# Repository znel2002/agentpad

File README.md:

# AgentPad

A 9-key macropad + rotary encoder + OLED for driving **AI coding agents** — Claude Code, Codex CLI, and Cursor. Firmware-native (no host daemon), vendor-neutral, with a per-tool **LAYER** key instead of app-detection. Built for **Hack Club Hackpad**.

## What it does

Nine keys mapped to the actions you hit dozens of times an hour when driving an agent, plus a rotary dial and a status screen:

| | | |
|---|---|---|
| **STOP** (interrupt) | **YES** (approve) | **NO** (reject) |
| **PLAN** (mode toggle) | **NEW** (`/clear`) | **TALK** (push-to-talk) |
| **RUN** (test/last cmd) | **COMPACT** (`/compact`) | **LAYER** (switch tool) |

- **Encoder** — turn = model / reasoning-effort dial.
- **OLED** — shows the active tool profile + mode.
- **LAYER key** — cycles per-tool keymaps: **Claude Code → Codex → Cursor → shell**. Each key sends that tool's real shortcut; hold-LAYER reaches secondary actions (accept-edit, reject-edit, resume, background). No daemon, no app-detection.

Full keymap + pin map: [docs/DESIGN-SPEC.md](docs/DESIGN-SPEC.md). Keymap logic is unit-tested: [Firmware/tests/sim_keymap.py](Firmware/tests/sim_keymap.py).

## Hardware

- **MCU:** Seeed XIAO RP2040 (all 11 GPIO used)
- **Keys:** 9× MX in a 3×3 diode matrix (9× 1N4148, COL2ROW)
- **Encoder:** 1× EC11 (turn-only)
- **Display:** 1× 0.91" SSD1306 OLED (I2C)
- **Firmware:** KMK (CircuitPython)
- **RGB:** deferred to v2 (v1 ships without LEDs)

## Renders & proof

**Exploded — top plate / PCB / bottom tray**

**Schematic**

**PCB — DRC passes with 0 errors**

## Bill of Materials

All parts come from the free Hackpad kit (nothing self-sourced):

| Part | Qty | Notes |
|---|---|---|
| Seeed XIAO RP2040 | 1 | microcontroller |
| 1N4148 diode | 9 | switch matrix, COL2ROW, `D_DO-35_SOD27_P7.62mm` |
| MX-style switch | 9 | solder-in, 3×3 grid @ 19.05 mm |
| EC11 rotary encoder | 1 | model / effort dial |
| 0.91" OLED (SSD1306) | 1 | I2C, pin order GND-VCC-SCL-SDA |
| DSA blank keycap | 9 | color/legend via a printed card |
| M3 screw | 4 | lid → base corner posts |

## Repo structure

```
CAD/         agentpad-case.f3d (Fusion source), agentpad_assembly.step/.3mf (case + real PCB), board STEP
PCB/         KiCad project — schematic, board (DRC 0 errors), Hack Club care-package libs
Firmware/    KMK source (kmk/main.py) + keymap simulation test
production/  gerbers.zip, top_plate.stl, bottom_tray.stl, main.py
docs/        DESIGN-SPEC, BUILD-PLAN, screenshots
```

## Firmware (KMK)

Flash CircuitPython to the XIAO, copy the KMK `kmk/` folder + libs + [`Firmware/kmk/main.py`](Firmware/kmk/main.py) to the `CIRCUITPY` drive. Details + per-layer keystroke tables: [Firmware/README.md](Firmware/README.md).

## Case

3D-printed two-part sandwich — **top lid + bottom base** — designed in **Autodesk Fusion** ([CAD/agentpad-case.f3d](CAD/agentpad-case.f3d)) around the exact PCB (imported as STEP). Both parts print flat with no supports.

- **Lid:** recessed key well inside a raised bezel; 9 switch cutouts with chamfered mouths, an encoder hole, and an OLED window; rounded R6 corners.
- **Base:** holds the PCB on corner posts; USB-C exits a slot in the side wall; **AgentPad** engraved on the front wall; matching R6 corners and chamfered top edge.
- **Assembly:** 4× M3 screws through the lid into the base's corner posts.

Fit is verified against the real board geometry — switch cutouts sit exactly on the switch stems, and screw holes align to the base bosses.

## License

MIT — see notes; the vendored Hack Club care package under `PCB/lib/` retains its own license.

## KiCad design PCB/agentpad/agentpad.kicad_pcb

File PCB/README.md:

# PCB — AgentPad

KiCad source for the AgentPad board. Design locked in
[../docs/DESIGN-SPEC.md](../docs/DESIGN-SPEC.md).

## Before you start
1. KiCad **10.0.5** is installed. Its libraries are forward-compatible, so the
   care package (authored on an older version) loads fine — no version issue.
2. Download + install the libraries here:
   - **Care package** (XIAO symbol + footprints): https://github.com/hackclub/hackpad/releases/tag/v0.1-bugfix → `kicad_care_package.zip`
   - XIAO footprints (backup): https://github.com/Seeed-Studio/OPL_Kicad_Library
   - MX switch footprints: https://github.com/ai03-2725/MX_V2
   - Rotary encoder: https://kicad.github.io/footprints/Rotary_Encoder
   - 0.91" OLED (4-pin): https://github.com/gorbachev/KiCad-SSD1306-0.91-OLED-4pin-128x32.pretty
   - The `.sym` files are symbol libs; the `.pretty` folders are footprint libs
     (Preferences → Manage Symbol/Footprint Libraries → add).
3. **Reference board** — the guide author's macropad (OLED + encoder + matrix +
   SK6812, closest to ours): https://github.com/hackclub/hackpad/tree/clean/extras/orpheuspad
4. Learn the flow: ai03's PCB guide https://wiki.ai03.com/books/pcb-design
5. Build the 3-key tutorial board first (XIAO symbol = `MODULE-SEEEDUINO-XIAO`,
   switches = `SW_Push`) to validate the toolchain, then extend to this net map.

## Net map — XIAO RP2040 pad → net (all 11 GPIO used)

| Pad | GPIO | Net |
|---|---|---|
| D0 | GP26 | ROW0 |
| D1 | GP27 | ROW1 |
| D2 | GP28 | ROW2 |
| D3 | GP29 | LED_DIN (SK6812 chain data-in) |
| D4 | GP6 | OLED_SDA (I2C) |
| D5 | GP7 | OLED_SCL (I2C) |
| D6 | GP0 | COL0 |
| D7 | GP1 | COL1 |
| D8 | GP2 | COL2 |
| D9 | GP4 | ENC_A |
| D10 | GP3 | ENC_B |
| 3V3 | — | OLED VCC |
| **5V** | — | **all SK6812 VCC** (the LEDs are 5V parts, per the Hackpad add-components page) |
| GND | — | matrix/encoder commons, OLED GND, all SK6812 GND |

> Data logic stays at the XIAO's 3.3V; SK6812 run their VCC at 5V (the XIAO's 5V/USB
> pad). This is how the kit is designed — do not put SK6812 VCC on 3V3.

## Exact symbols / footprints (confirmed on hackpad.hackclub.com/add-components)

Verified against the unpacked care package in `lib/kicad_care_package/`. The care
package holds **only** the XIAO + SK6812; everything else is a KiCad built-in lib.

| Part | Symbol | Footprint | Source |
|---|---|---|---|
| XIAO RP2040 | `MOUDLE-SEEEDUINO-XIAO` *(sic — typo is in the file, search it literally)* | `XIAO-Generic-Hybrid-14P-2.54-21X17.8MM` | care package |
| SK6812 MINI-E | `SK6812MINI-E` | `SK6812MINI-E_fixed` | care package |
| MX switch | `SW_Push` | `ai03-2725/MX_V2` (or KiCad `Button_Switch_Keyboard`) | KiCad / MX_V2 |
| Diode 1N4148 | `D` | `Diode_THT:D_DO-35_SOD27_P7.62mm_Horizontal` (don't go shorter) | KiCad built-in |
| EC11 encoder | `RotaryEncoder_Switch` | `RotaryEncoder_Alps_EC11E-Switch_Vertical_H20mm` | KiCad built-in |
| 0.91" OLED | 4-pin header (`Connector_Generic`) | `PinHeader_1x04_P2.54mm_Vertical` | KiCad built-in |

No pull-up resistors anywhere — the RP2040 has internal pull-ups (kit relies on this).

## Matrix (3×3, 9 keys)
- One **1N4148** (onsemi) per key, all the **same orientation (COL2ROW)**. Wrong
  diode direction is the #1 beginner failure — verify against the KMK config
  (`Firmware/kmk/main.py`, `diode_orientation = COL2ROW`). The physical diode has
  a **black bar** marking the cathode.
- Footprint `Diode_THT:D_DO-35_SOD27_P7.62mm_Horizontal`.
- Keys map row-major to the keymap: R1C1..R1C3, R2C1..R2C3, R3C1..R3C3.

## Encoder (EC11E, 20 mm D-shaft)
- Symbol `RotaryEncoder_Switch`, footprint `RotaryEncoder_Alps_EC11E-Switch_Vertical_H20mm`.
- A → ENC_A (D9), B → ENC_B (D10), common → GND. No pull-ups needed.
- **Turn-only config:** the footprint includes the push-switch pins — leave them
  **unconnected**. Keeping the pads means an 8-key clickable variant is possible
  later without a respin.

## OLED (0.91" 128×32 SSD1306, I2C @ 0x3C)
- Footprint = plain **2.54 mm 4-pin header** (the module has a standard header;
  no special footprint needed).
- **Pin order GND-VCC-SCL-SDA** — match it exactly (online pinouts vary).
- SDA→D4, SCL→D5, VCC→3V3, GND→GND. No pull-ups needed.

## SK6812 MINI-E chain (20 LEDs, 1 data line)
- Footprint `SK6812MINI-E` from the care package (**not** `SK6812MINI`; symbol +
  both footprints must say MINI-E).
- 4 pins: VCC (**5V**), GND, DIN, DOUT. D3 → LED1 DIN; each DOUT → next DIN; chain all 20.
- **Orientation: the notch/cut is on the bottom-right corner** — wrong rotation and
  the LEDs won't light. Keep every LED the same way.
- 9 per-key (under each switch) + up to 11 case underglow.
- Keep the data trace from the XIAO to LED1 short.

## Mounting holes (from the Hackpad resources page)
- Use KiCad's **M3 mounting-hole footprint** — NOT Edge.Cuts.
- 6 holes to match the 6× M3 screws / heatset inserts.
- For the OLED, a plain **4-pin header footprint** is fine (order GND-VCC-SCL-SDA).

## Routing tips (from the resources page)
- Try to route everything on **one layer** first; only drop to the 2nd layer to
  avoid a big loop. Keeps the board clean.
- After routing: **Tools → Cleanup Tracks & Vias** (press "Build changes" twice).
- Export the PCB to PDF and print 1:1 to sanity-check physical measurements.

## Preflight before ordering
- [ ] Board ≤ 100 × 100 mm, **2 layers**.
- [ ] `AgentPad` on the silkscreen.
- [ ] 6× M3 mounting-hole footprints placed.
- [ ] **DRC → 0 errors** (reviewers check this).
- [ ] Export gerbers → `../production/gerbers.zip`.
- [ ] Order JLCPCB immediately after DRC is clean.

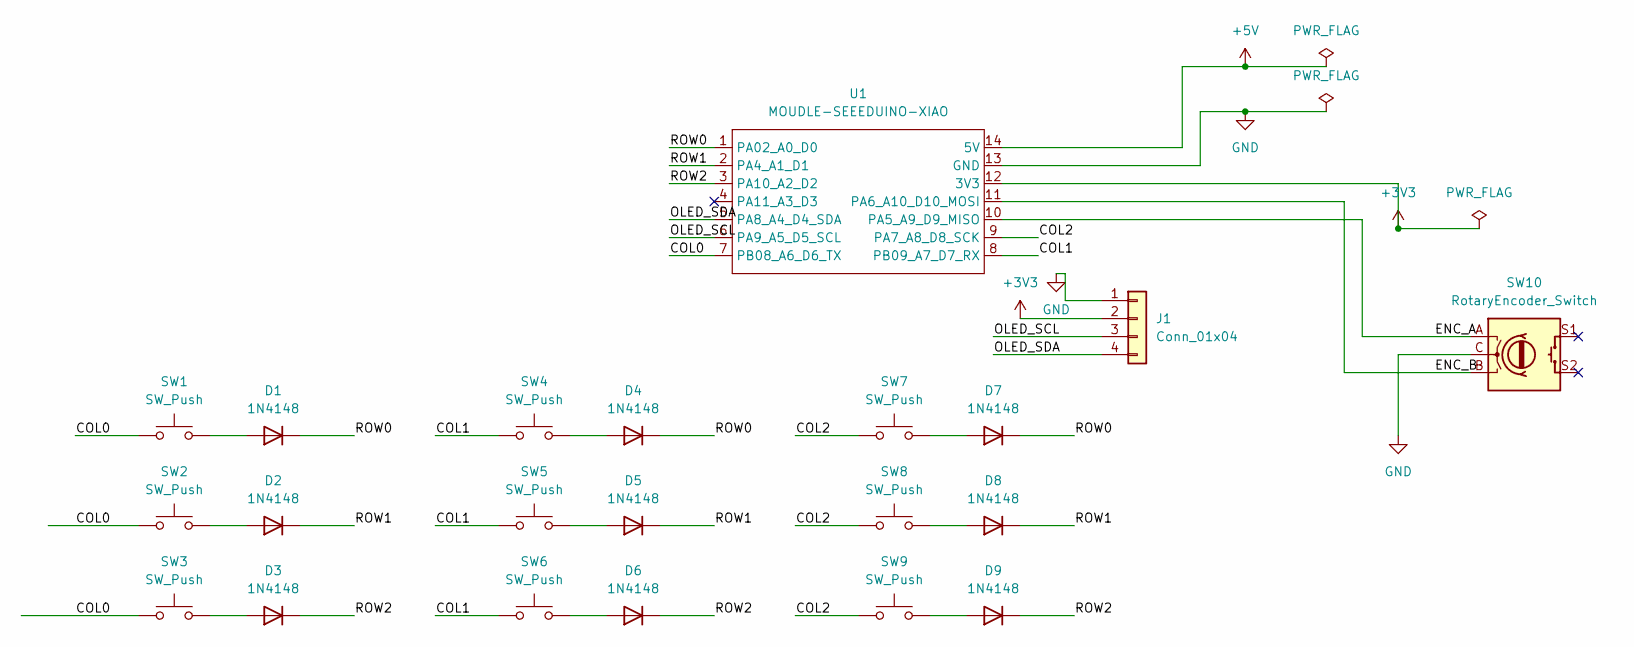
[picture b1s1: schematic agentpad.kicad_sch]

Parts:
D1, D2, D3, D4, D5, D6, D7, D8, D9: 1N4148; D_DO-35_SOD27_P7.62mm_Horizontal
J1: Conn_01x04; PinHeader_1x04_P2.54mm_Vertical
SW1, SW2, SW3, SW4, SW5, SW6, SW7, SW8, SW9: SW_Push; SW_Cherry_MX_1.00u_PCB
SW10: RotaryEncoder_Switch; RotaryEncoder_Alps_EC11E-Switch_Vertical_H20mm
U1: MOUDLE-SEEEDUINO-XIAO; XIAO-Generic-Hybrid-14P-2.54-21X17.8MM

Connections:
+3V3: J1.2, U1.12 (3V3)
+5V: U1.14 (5V)
/COL0: SW1.1, SW2.1, SW3.1, U1.7 (PB08_A6_D6_TX)
/COL1: SW4.1, SW5.1, SW6.1, U1.8 (PB09_A7_D7_RX)
/COL2: SW7.1, SW8.1, SW9.1, U1.9 (PA7_A8_D8_SCK)
/ENC_A: SW10.A, U1.10 (PA5_A9_D9_MISO)
/ENC_B: SW10.B, U1.11 (PA6_A10_D10_MOSI)
/OLED_SCL: J1.3, U1.6 (PA9_A5_D5_SCL)
/OLED_SDA: J1.4, U1.5 (PA8_A4_D4_SDA)
/ROW0: D1.1 (K), D4.1 (K), D7.1 (K), U1.1 (PA02_A0_D0)
/ROW1: D2.1 (K), D5.1 (K), D8.1 (K), U1.2 (PA4_A1_D1)
/ROW2: D3.1 (K), D6.1 (K), D9.1 (K), U1.3 (PA10_A2_D2)
GND: J1.1, SW10.C, U1.13 (GND)
unnamed: D1.2 (A), SW1.2
unnamed: D2.2 (A), SW2.2
unnamed: D3.2 (A), SW3.2
unnamed: D4.2 (A), SW4.2
unnamed: D5.2 (A), SW5.2
unnamed: D6.2 (A), SW6.2
unnamed: D7.2 (A), SW7.2
unnamed: D8.2 (A), SW8.2
unnamed: D9.2 (A), SW9.2

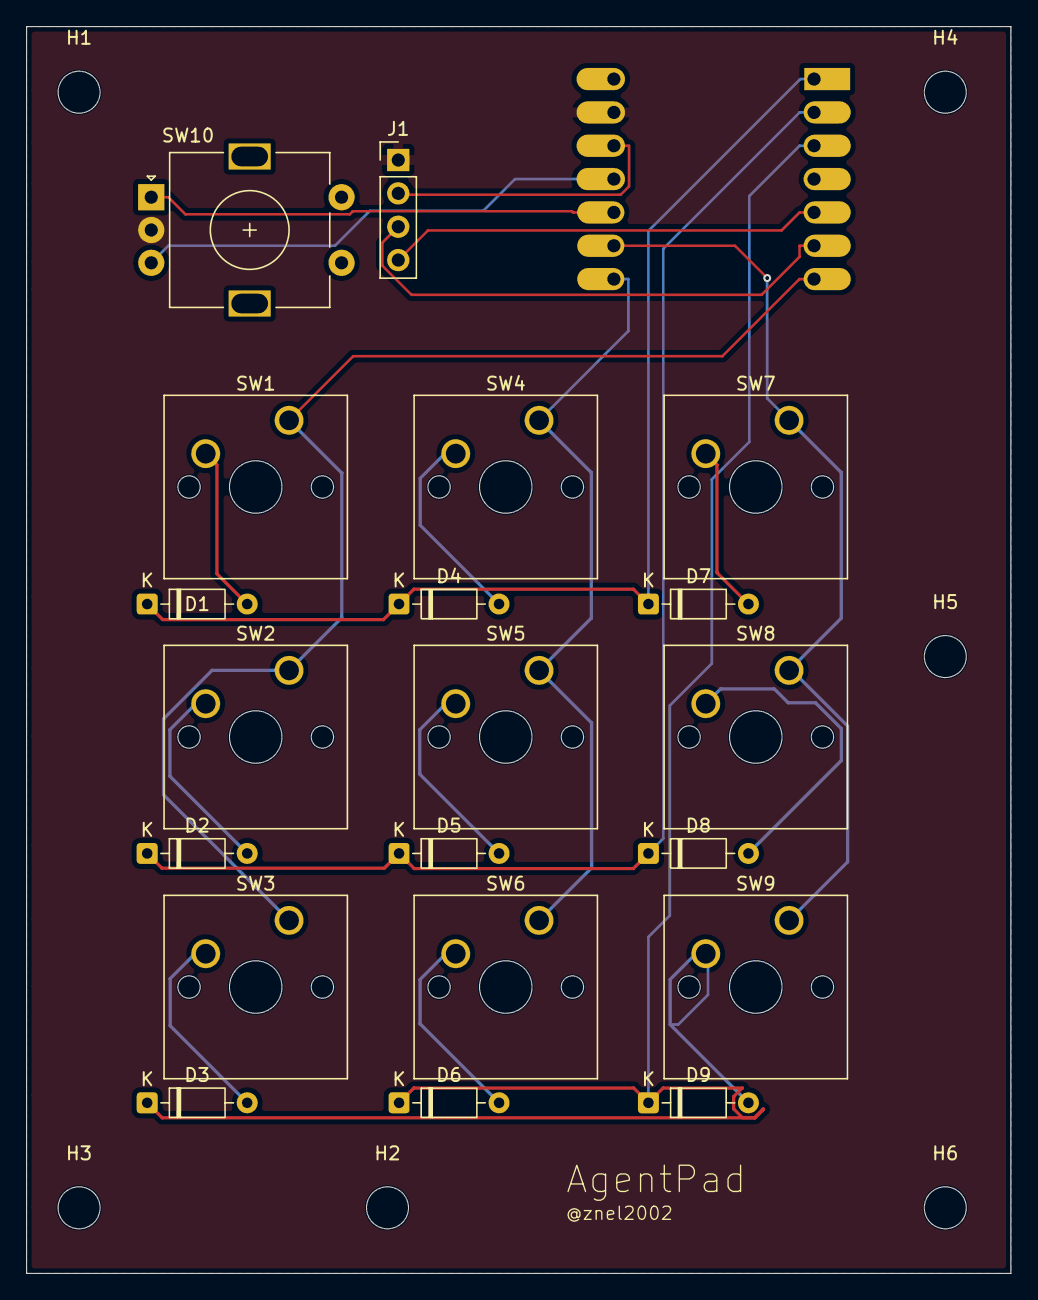
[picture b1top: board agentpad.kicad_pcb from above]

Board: 2 copper layers, 75.0 x 95.0 mm, 27 parts (1 on the bottom side), 21 nets.

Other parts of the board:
H1, H2, H3, H4, H5, H6: MountingHole_3.2mm_M3
